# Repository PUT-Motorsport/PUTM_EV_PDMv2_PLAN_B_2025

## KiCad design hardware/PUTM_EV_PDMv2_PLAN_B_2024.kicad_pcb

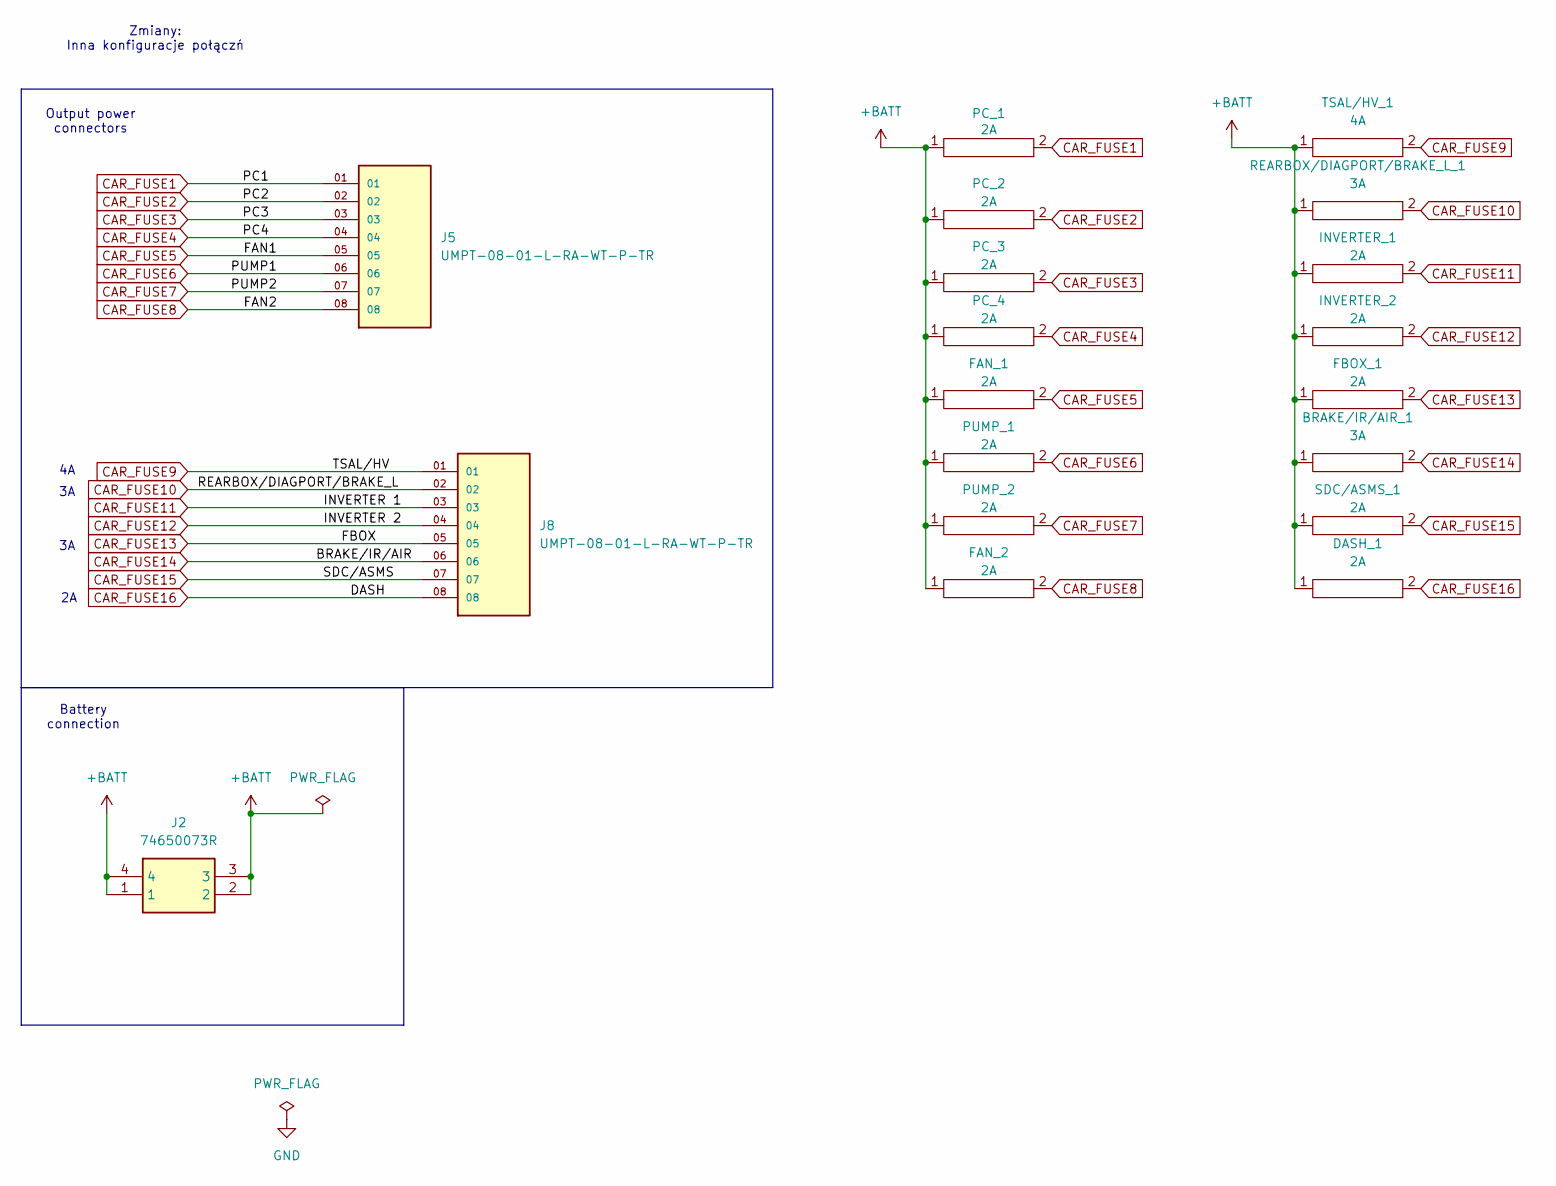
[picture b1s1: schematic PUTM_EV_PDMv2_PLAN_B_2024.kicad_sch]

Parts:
BRAKE/IR/AIR_1: 3A; CAR_FUSE_CLIPS_MINI_3544
DASH_1: 2A; CAR_FUSE_CLIPS_MINI_3544
FAN_1, FAN_2: 2A; CAR_FUSE_CLIPS_MINI_3544
FBOX_1: 2A; CAR_FUSE_CLIPS_MINI_3544
INVERTER_1, INVERTER_2: 2A; CAR_FUSE_CLIPS_MINI_3544
J2: 74650073R; Mouser Part Number 710-74650073R
J5, J8: UMPT-08-01-L-RA-WT-P-TR; SAMTEC_UMPT-08-01-L-RA-WT-P-TR
PC_1, PC_2, PC_3, PC_4: 2A; CAR_FUSE_CLIPS_MINI_3544
PUMP_1, PUMP_2: 2A; CAR_FUSE_CLIPS_MINI_3544
REARBOX/DIAGPORT/BRAKE_L_1: 3A; CAR_FUSE_CLIPS_MINI_3544
SDC/ASMS_1: 2A; CAR_FUSE_CLIPS_MINI_3544
TSAL/HV_1: 4A; CAR_FUSE_CLIPS_MINI_3544

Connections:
+BATT: BRAKE/IR/AIR_1.1, DASH_1.1, FAN_1.1, FAN_2.1, FBOX_1.1, INVERTER_1.1, INVERTER_2.1, J2.1, J2.2, J2.3, J2.4, PC_1.1, PC_2.1, PC_3.1, PC_4.1, PUMP_1.1, PUMP_2.1, REARBOX/DIAGPORT/BRAKE_L_1.1, SDC/ASMS_1.1, TSAL/HV_1.1
CAR_FUSE1: J5.01, PC_1.2
CAR_FUSE2: J5.02, PC_2.2
CAR_FUSE3: J5.03, PC_3.2
CAR_FUSE4: J5.04, PC_4.2
CAR_FUSE5: FAN_1.2, J5.05
CAR_FUSE6: J5.06, PUMP_1.2
CAR_FUSE7: J5.07, PUMP_2.2
CAR_FUSE8: FAN_2.2, J5.08
CAR_FUSE9: J8.01, TSAL/HV_1.2
CAR_FUSE10: J8.02, REARBOX/DIAGPORT/BRAKE_L_1.2
CAR_FUSE11: INVERTER_1.2, J8.03
CAR_FUSE12: INVERTER_2.2, J8.04
CAR_FUSE13: FBOX_1.2, J8.05
CAR_FUSE14: BRAKE/IR/AIR_1.2, J8.06
CAR_FUSE15: J8.07, SDC/ASMS_1.2
CAR_FUSE16: DASH_1.2, J8.08

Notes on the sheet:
Output power connectors
Zmiany: Inna konfiguracje połączń
Battery connection

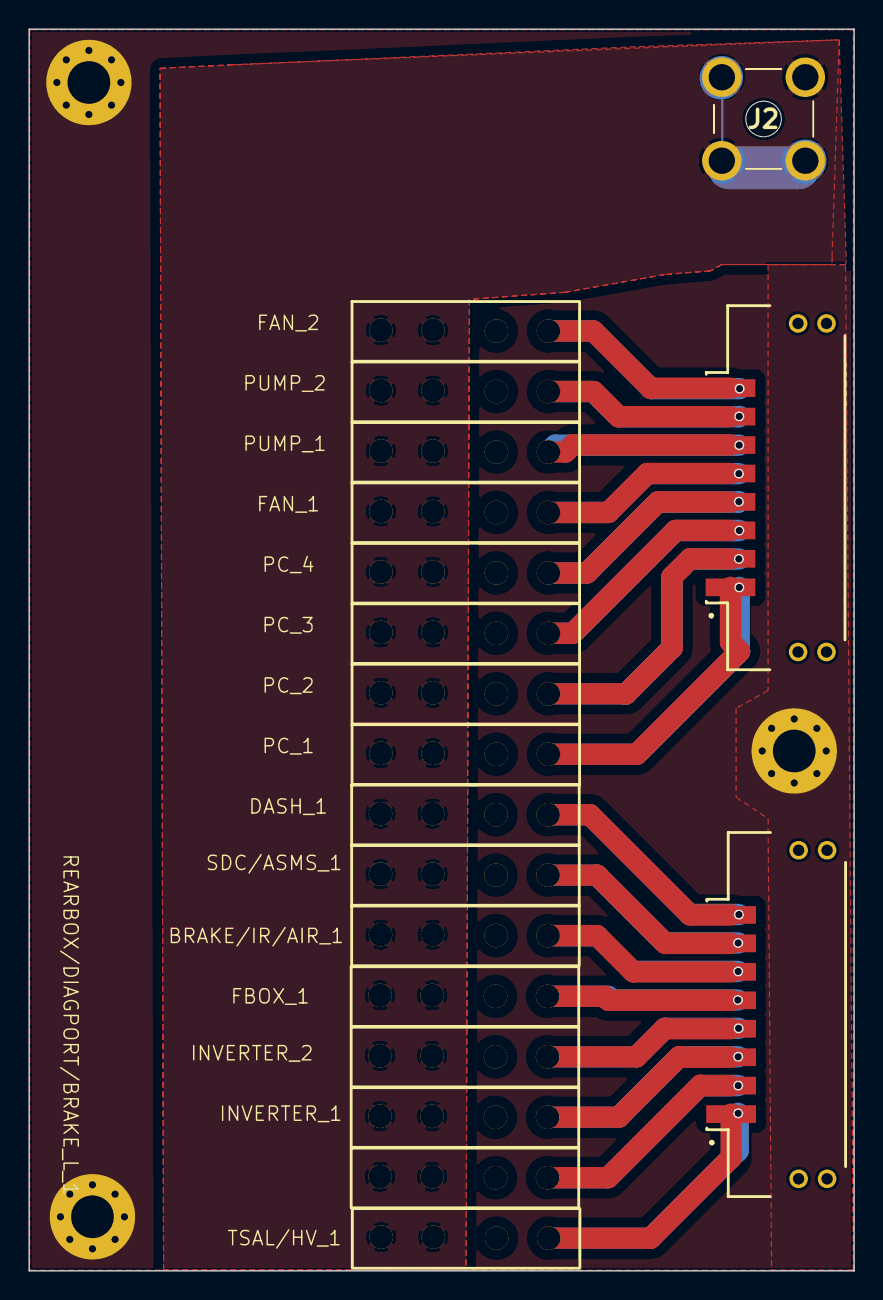
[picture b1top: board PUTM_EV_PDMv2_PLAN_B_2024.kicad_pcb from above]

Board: 2 copper layers, 58.0 x 87.3 mm, 19 parts (0 on the bottom side), 17 nets.

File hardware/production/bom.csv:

Designator,Footprint,Quantity,Value,LCSC Part #
"BRAKE/IR/AIR_1, REARBOX/DIAGPORT/BRAKE_L_1",CAR_FUSE_CLIPS_MINI_3544,2,3A,
"DASH_1, FAN_1, FAN_2, FBOX_1, INVERTER_1, INVERTER_2, PC_1, PC_2, PC_3, PC_4, PUMP_1, PUMP_2, SDC/ASMS_1",CAR_FUSE_CLIPS_MINI_3544,13,2A,
J2,74650073R,1,74650073R,
"J5, J8",SAMTEC_UMPT-08-01-L-RA-WT-P-TR,2,UMPT-08-01-L-RA-WT-P-TR,
TSAL/HV_1,CAR_FUSE_CLIPS_MINI_3544,1,4A,

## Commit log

2025-05-27 Version_1
2025-05-27 Version_after_fix
2025-05-27 Version_after_fix2
2025-05-28 Version_production
2025-05-28 Production version fix
